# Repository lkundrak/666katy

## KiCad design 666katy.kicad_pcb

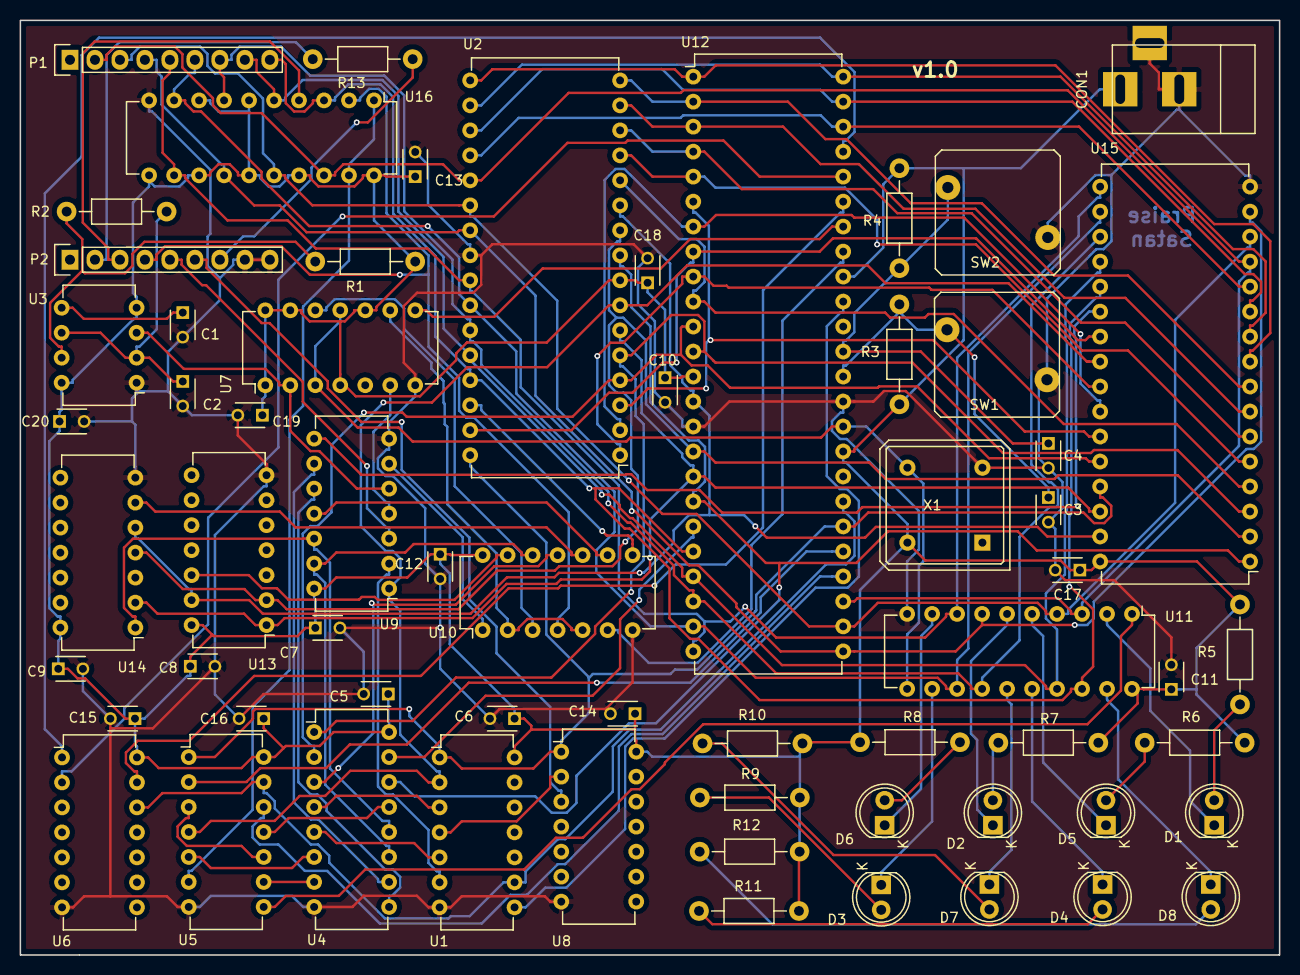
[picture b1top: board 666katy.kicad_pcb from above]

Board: 2 copper layers, 128.0 x 95.0 mm, 63 parts (0 on the bottom side), 94 nets.

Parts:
C1: 100 pF; C_Disc_D3_P2.5
C2: 0.47 uF; C_Disc_D3_P2.5
C3, C4: 1 uF; C_Disc_D3_P2.5
C5, C6, C7, C8, C9, C10, C11, C12, C13, C14, C15, C16, C17, C18, C19, C20: 0.1 uF; C_Disc_D3_P2.5
CON1: BARREL_JACK
D1, D2, D3, D4, D5, D6, D7, D8: Led_Small; LED-5MM
P1: FT24RL JP1; Pin_Header_Straight_1x09
P2: FT24RL JP2; Pin_Header_Straight_1x09
R1, R2, R3, R4: 10 k; Resistor_Horizontal_RM10mm
R5, R6, R7, R8, R9, R10, R11, R12: 330; Resistor_Horizontal_RM10mm
R13: 10 K; Resistor_Horizontal_RM10mm
SW1: HALT; SW_PUSH
SW2: RESET; SW_PUSH
U1: 74LS04; DIP-14_W7.62mm
U2: 29W040; DIP-32_W15.24mm
U3: LM555N; DIP-8_W7.62mm
U4: 74LS139; DIP-16_W7.62mm
U5, U10: 74LS32; DIP-14_W7.62mm
U6: 74LS11; DIP-14_W7.62mm
U7: 74HC74; DIP-14_W7.62mm
U8: 7400; DIP-14_W7.62mm
U9: 74LS08; DIP-14_W7.62mm
U11: 74LS377; DIP-20_W7.62mm
U12: 68008D; DIP-48_W15.24mm
U13: 74LS10; DIP-14_W7.62mm
U14: 74LS21; DIP-14_W7.62mm
U15: SRAM_512Ko; DIP-32_W15.24mm
U16: 74LS244; DIP-20_W7.62mm
X1: 12 MHz; OSC_DIP8

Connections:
+5V: C5.1, C6.1, C7.1, C8.1, C9.1, C10.1, C11.1, C12.1, C13.1, C14.1, C15.1, C16.1, C17.1, C18.1, C19.1, C20.1, CON1.1, R1.1, R3.1, R4.1, R5.1, R6.1, R7.1, R8.1, R9.1, R10.1, R11.1, R12.1, U1.14, U2.8, U3.4, U3.8, U4.16, U5.14, U6.14, U7.1, U7.4, U7.10, U7.13, U7.14, U8.14, U9.14, U10.14, U11.20, U12.13, U12.33, U12.40, U13.14, U14.14, U15.32, U16.6, U16.8, U16.11, U16.13, U16.15, U16.17, U16.20, X1.8
/A0: U2.20, U12.46, U15.12
/A1: U2.19, U12.47, U15.11
/A2: U2.18, U12.48, U15.10
/A3: U2.17, U12.1, U15.9
/A4: U2.16, U12.2, U15.8
/A5: U2.15, U12.3, U15.7
/A6: U2.14, U12.4, U15.6
/A7: U2.13, U12.5, U15.5
/A8: U2.3, U12.6, U15.27
/A9: U2.2, U12.7, U15.26
/A10: U2.31, U12.8, U15.23
/A11: U2.1, U12.9, U15.25
/A12: U2.12, U12.10, U15.4
/A13: U2.4, U4.2, U12.11, U15.28
/A14: U2.5, U4.1, U12.12, U15.3
/A15: U2.11, U12.14, U13.13, U14.5, U15.31
/A16: U2.10, U12.16, U13.2, U14.4, U15.2
/A17: U2.6, U12.17, U13.1, U14.2, U15.30
/A18: U2.9, U4.14, U12.18, U15.1
/A19: U4.15, U12.19
/CLK: U7.3, U7.11, U11.11, U12.34, X1.5
/D0: P1.2, U2.21, U11.3, U12.27, U15.13, U16.18
/D1: P1.3, U2.22, U11.4, U12.26, U15.14, U16.16
/D2: P1.4, U2.23, U11.7, U12.25, U15.15, U16.14
/D3: P1.5, U2.25, U11.8, U12.24, U15.17, U16.12
/D4: P1.6, U2.26, U11.13, U12.23, U15.18, U16.9
/D5: P1.7, U2.27, U11.14, U12.22, U15.19, U16.7
/D6: P1.8, U2.28, U11.17, U12.21, U15.20, U16.5
/D7: P1.9, U2.29, U11.18, U12.20, U15.21, U16.3
/FC0: U6.1, U12.45
/FC1: U6.2, U12.44
/FC2: U6.13, U12.43
/INTR: U1.9, U5.13, U6.12, U12.31
/RW: U1.1, U2.32, U5.1, U8.1, U12.30, U15.29
/SER_WR: P2.5, U9.3
/~AS~: U5.12, U12.28
/~CSRAM~: U9.8, U15.22
/~DEVICECS~: U4.3, U10.11
/~DS~: U5.2, U12.29
/~IP1~: U10.6, U12.41
/~IP2~: U7.8, U12.42
/~M0~: U4.12, U9.12, U14.1
/~M1~: U4.11, U9.13, U10.12
/~OESTATUS~: U5.6, U16.1, U16.19
/~OE~: U1.2, U2.7, U5.4, U9.1, U15.24
/~REGLD~: U5.8, U11.1
/~ROMCS~: U2.30, U10.8
/~RXF~: P2.4, U10.4, U16.2
/~SER_RD~: P2.6, U8.3
/~TIMER~: U3.3, U7.2, U9.5
/~TXF~: P2.3, U16.4
/~VPA~: U1.8, U12.39
GND: C1.2, C2.2, C3.2, C4.2, C5.2, C6.2, C7.2, C8.2, C9.2, C10.2, C11.2, C12.2, C13.2, C14.2, C15.2, C16.2, C17.2, C18.2, C19.2, C20.2, CON1.2, CON1.3, P2.8, P2.9, SW1.1, SW2.1, U1.7, U2.24, U3.1, U4.8, U5.7, U6.7, U7.7, U8.7, U9.7, U10.7, U11.10, U12.15, U12.35, U13.7, U14.7, U15.16, U16.10, X1.4
unnamed: C1.1, U3.5
unnamed: C2.1, R2.2, U3.2, U3.6
unnamed: C3.1, R3.2, SW1.2, U12.36
unnamed: C4.1, R4.2, SW2.2, U12.37
unnamed: D1.1, U11.2
unnamed: D1.2, R5.2
unnamed: D2.1, U11.6
unnamed: D2.2, R7.2
unnamed: D3.1, U11.12
unnamed: D3.2, R9.2
unnamed: D4.1, U11.16
unnamed: D4.2, R11.2
unnamed: D5.1, U11.5
unnamed: D5.2, R6.2
unnamed: D6.1, U11.9
unnamed: D6.2, R8.2
unnamed: D7.1, U11.15
unnamed: D7.2, R10.2
unnamed: D8.1, U11.19
unnamed: D8.2, R12.2
unnamed: P2.2, R13.1
unnamed: P2.7, R13.2
unnamed: R1.2, R2.1, U3.7
unnamed: U1.3, U4.4
unnamed: U1.4, U8.2
unnamed: U1.5, U4.5
unnamed: U1.6, U9.2
unnamed: U4.6, U5.5
unnamed: U4.7, U5.9
unnamed: U4.9, U9.10
unnamed: U4.10, U9.9
unnamed: U4.13, U5.11
unnamed: U5.3, U5.10
unnamed: U7.6, U9.4
unnamed: U9.6, U10.1
unnamed: U7.9, U10.2, U10.5
unnamed: U7.12, U10.3
unnamed: U9.11, U10.9
unnamed: U10.10, U14.6
unnamed: U10.13, U13.12
